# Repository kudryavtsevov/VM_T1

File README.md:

# VM-T1 F1Q — ESP32-C3 Super Mini

Отдельная ветка **`f1q-esp32-c3-super-mini`** для недорогого открытого таймера F1Q.
Исходный проект таймера — **Мстислав**, опубликован с его разрешения под Apache-2.0.
Основная ветка `main` сохраняет исходный проект ESP32-S3; эта ветка использует другую распиновку и логику старта.

## Что подготовлено

- ESP32-C3 Super Mini устанавливается на плату двумя рядами по 8 контактов, шаг 2,54 мм, междурядье 15,24 мм.
- Три сервопривода, отдельный ESC, кнопки ARM/START/OFF/RC DT.
- INA226: ток, напряжение, энергия; BMP280: относительная высота и максимум.
- Экспериментальный лимиттер по энергии и времени с блокировкой повторного запуска.
- Настройка через Wi-Fi. Концевики BACK/FRONT в F1Q не используются.

**Для двигателя около 7 А нужно физически заменить R100 на R010 (0,01 Ом, от 2 Вт).**
Рабочий предел 7,5 А, диапазон АЦП около 8,19 А. Пусковые пики и нагрев требуют стендового измерения.
Режим F1Q по умолчанию выключен. Это прототип, **одобрения EDIC и аппаратных испытаний нет**.

## Документация и плата

- [Размеры, ориентация двух рядов и GPIO C3](docs/C3_GEOMETRY.md).
- [Подключение R010, BMP280 и порядок испытаний](docs/F1Q.md).
- [Готовые модули в России](docs/BUY_RU.md).
- [KiCad, схема, Gerber и монтажный эскиз платы C3](hardware/c3-supermini-v1/README.md).
- [Лицензия и зависимости](LICENSING.md).

Старые PDF и `hardware/carrier-v1` относятся к исходному таймеру/S3 и не являются инструкцией для C3.

## Arduino IDE

Открыть `VM_T1/VM_T1.ino`. Папка и основной файл должны иметь одинаковое имя `VM_T1`.

1. В менеджер плат добавить `https://espressif.github.io/arduino-esp32/package_esp32_index.json`.
2. Установить **esp32 by Espressif Systems 2.0.11**.
3. Библиотеки: **ESP32Servo 1.1.2**, **ArduinoJson 7.4.3**, **Adafruit BMP280 Library 2.6.8**, **Adafruit BusIO 1.17.4**, **Adafruit Unified Sensor 1.1.15**.
4. Плата **ESP32C3 Dev Module**; USB CDC On Boot **Enabled**, Flash Mode **DIO**, Upload Speed **115200**. PSRAM для C3 не требуется.
5. Verify, затем выбрать порт и Upload. При необходимости входа в загрузчик удержать BOOT, нажать и отпустить RESET, затем отпустить BOOT.

```sh
arduino-cli compile --fqbn "esp32:esp32:esp32c3:CDCOnBoot=cdc,FlashMode=dio,UploadSpeed=115200" VM_T1
```

При включении со снятым ARM точка Wi-Fi работает три минуты. Повторно: снять ARM и держать OFF три секунды.
GPIO9/BOOT не занят периферией. Прошивка отклоняет сборку для S3, чтобы не прошить несовместимую распиновку.
Версии Core 3.x этой проверкой не подтверждены.

## Проверки

Arduino CLI 0.35.3: сборка C3 проверена — 806 276 байт Flash, 39 972 байта RAM. Подробности итоговых проверок — в `hardware/c3-supermini-v1/README.md`.
Автономные тесты расчёта энергии находятся в `tests/`. Проверка геометрии, назначения GPIO и совпадения схемы с платой — `tools/verify_c3.py`.
Проверки на компьютере не заменяют калибровку и испытания физического устройства.

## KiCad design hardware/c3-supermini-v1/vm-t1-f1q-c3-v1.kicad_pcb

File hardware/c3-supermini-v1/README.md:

# VM-T1 F1Q: плата для ESP32-C3 Super Mini

Двухслойный прототип **40,64 × 76,2 мм**, FR-4 1,6 мм, медь 35 мкм.
Контроллер устанавливается непосредственно в **два разъёма 1×8**, расстояние между рядами 15,24 мм, шаг 2,54 мм.
Вид сверху: **USB вверх**, 5V в верхнем правом углу, GPIO5 — в верхнем левом.
[Источник геометрии, ориентация и таблица GPIO](../../docs/C3_GEOMETRY.md).

Штриховой контур показывает ориентировочный габарит модуля; точные посадочные размеры задаются центрами отверстий.
USB и положение контура относительно крайних выводов нужно сверить со своей ревизией платы; рисунок разъёма условный.
Между рядами и под центральной областью антенны задана зона без меди. Испытания радиосвязи не выполнены.

## Файлы

- `vm-t1-f1q-c3-v1.kicad_pro`, `.kicad_sch`, `.kicad_pcb` — проект, схема и разведённая плата KiCad 8.
- `VM_T1_C3.pretty`, `VM_T1_C3.kicad_sym`, таблицы библиотек — локальные библиотеки.
- `gerbers/`, `vm-t1-f1q-c3-v1-gerbers.zip` — Gerber и сверловка для пробного изготовления.
- `assembly.svg`, `assembly.png` — монтажный эскиз, построенный из координат платы.
- `drc.json`, `erc.json` — результаты проверок.

## Комплектующие и подключение

| Обозначение | Что установить / подключить |
|---|---|
| U1 | ESP32-C3 Super Mini, два гнезда 1×8, шаг 2,54 мм |
| J1 | INA226: слева направо 3V3, GND, SDA, SCL |
| J2 | BMP280: слева направо 3V3, GND, SDA, SCL |
| J3 / J4 / J5 | Servo S / R / W: GND, +5V, сигнал |
| J6 | ESC: GND и сигнал; средний контакт питания отсутствует |
| J7 / J8 | ARM / START: GND и сигнал |
| J9 / J10 | OFF / RC DT: GND и сигнал |
| J11 | Управляющий вход модуля активной пищалки: GND и сигнал; питание модуля отдельно |
| J12 | BEC: GND и стабилизированные +5V |
| R1 | 47 кОм, выводной, шаг 7,62 мм — подтяжка сигнала ESC к GND |
| R2 / R3 | 4,7 кОм, выводные, шаг 7,62 мм — подтяжки SDA/SCL к 3,3 В |

Если готовые датчики уже имеют подтяжки I²C, учесть их параллельное соединение: R2/R3 можно не устанавливать при наличии достаточных подтяжек на модулях. SDA GPIO2 должна иметь определённый высокий уровень при старте. Ориентир общего сопротивления подтяжек — 2,2–4,7 кОм; проверить фронты и обмен на своей проводке.

Светодиод используется встроенный в Super Mini. GPIO9/BOOT не подключён к периферии; оба отверстия GPIO8/9 присутствуют для штатной установки модуля. Датчики подключаются короткими проводами и закрепляются отдельно: геометрия их модулей не стандартизирована.

**Ток двигателя 7 А не проходит через эту плату.** Силовую цепь аккумулятор → R010 на INA226 → ESC выполнить отдельно подходящими проводами/контактами. 5V получает только выход BEC. Первоначально ограничить суммарный ток 5-вольтовых цепей платы до 1 А и проверить нагрев/просадки; мощные сервоприводы питать отдельной шиной с общей землёй. Нельзя соединять параллельно два выхода BEC или USB и внешнее питание без развязки.

На плате нет стабилизатора и защиты переполюсовки; монтажных отверстий нет. Использовать изолирующее крепление, исключить смещение модулей и контакт нижних выводов с проводкой. Для первого включения применять источник с ограничением тока.

## Проверки, 30 сентября 2026

- KiCad 8.0.2: **ERC 0, DRC 0, неподключённых цепей 0**.
- `tools/verify_c3.py`: проверены оба ряда 1×8, шаг и междурядье; 12 назначений GPIO без повторений; все 51 внешнее соединение схемы совпадают с фактической платой.
- Arduino CLI 0.35.3, Core 2.0.11: **806 276 байт Flash, 39 972 байта RAM**, успешная сборка. Осталось предупреждение Unicode старого генератора разделов Flash.
- Тесты расчёта энергии пройдены. Монтажный эскиз и экспорт платы просмотрены.

Эти проверки не подтверждают работу на оборудовании, тепловой режим, точность лимиттера или соответствие спортивным требованиям. До полётов выполнить [стендовые испытания](../../docs/F1Q.md). Это не одобренный EDIC лимиттер.

## Воспроизведение

Генератор `tools/generate_c3_carrier.py` запускается Python из KiCad 8. После генерации выполнить ERC/DRC, экспортировать netlist в формате `kicadxml`, затем запустить `tools/verify_c3.py <netlist.xml>` тем же Python. После изменений платы заново экспортировать Gerber и сверловку. Дорожки сигналов 0,3 мм, питания 0,8 мм, минимальный зазор 0,2 мм, сверловка выводов 1,0 мм, переходных отверстий 0,3 мм.

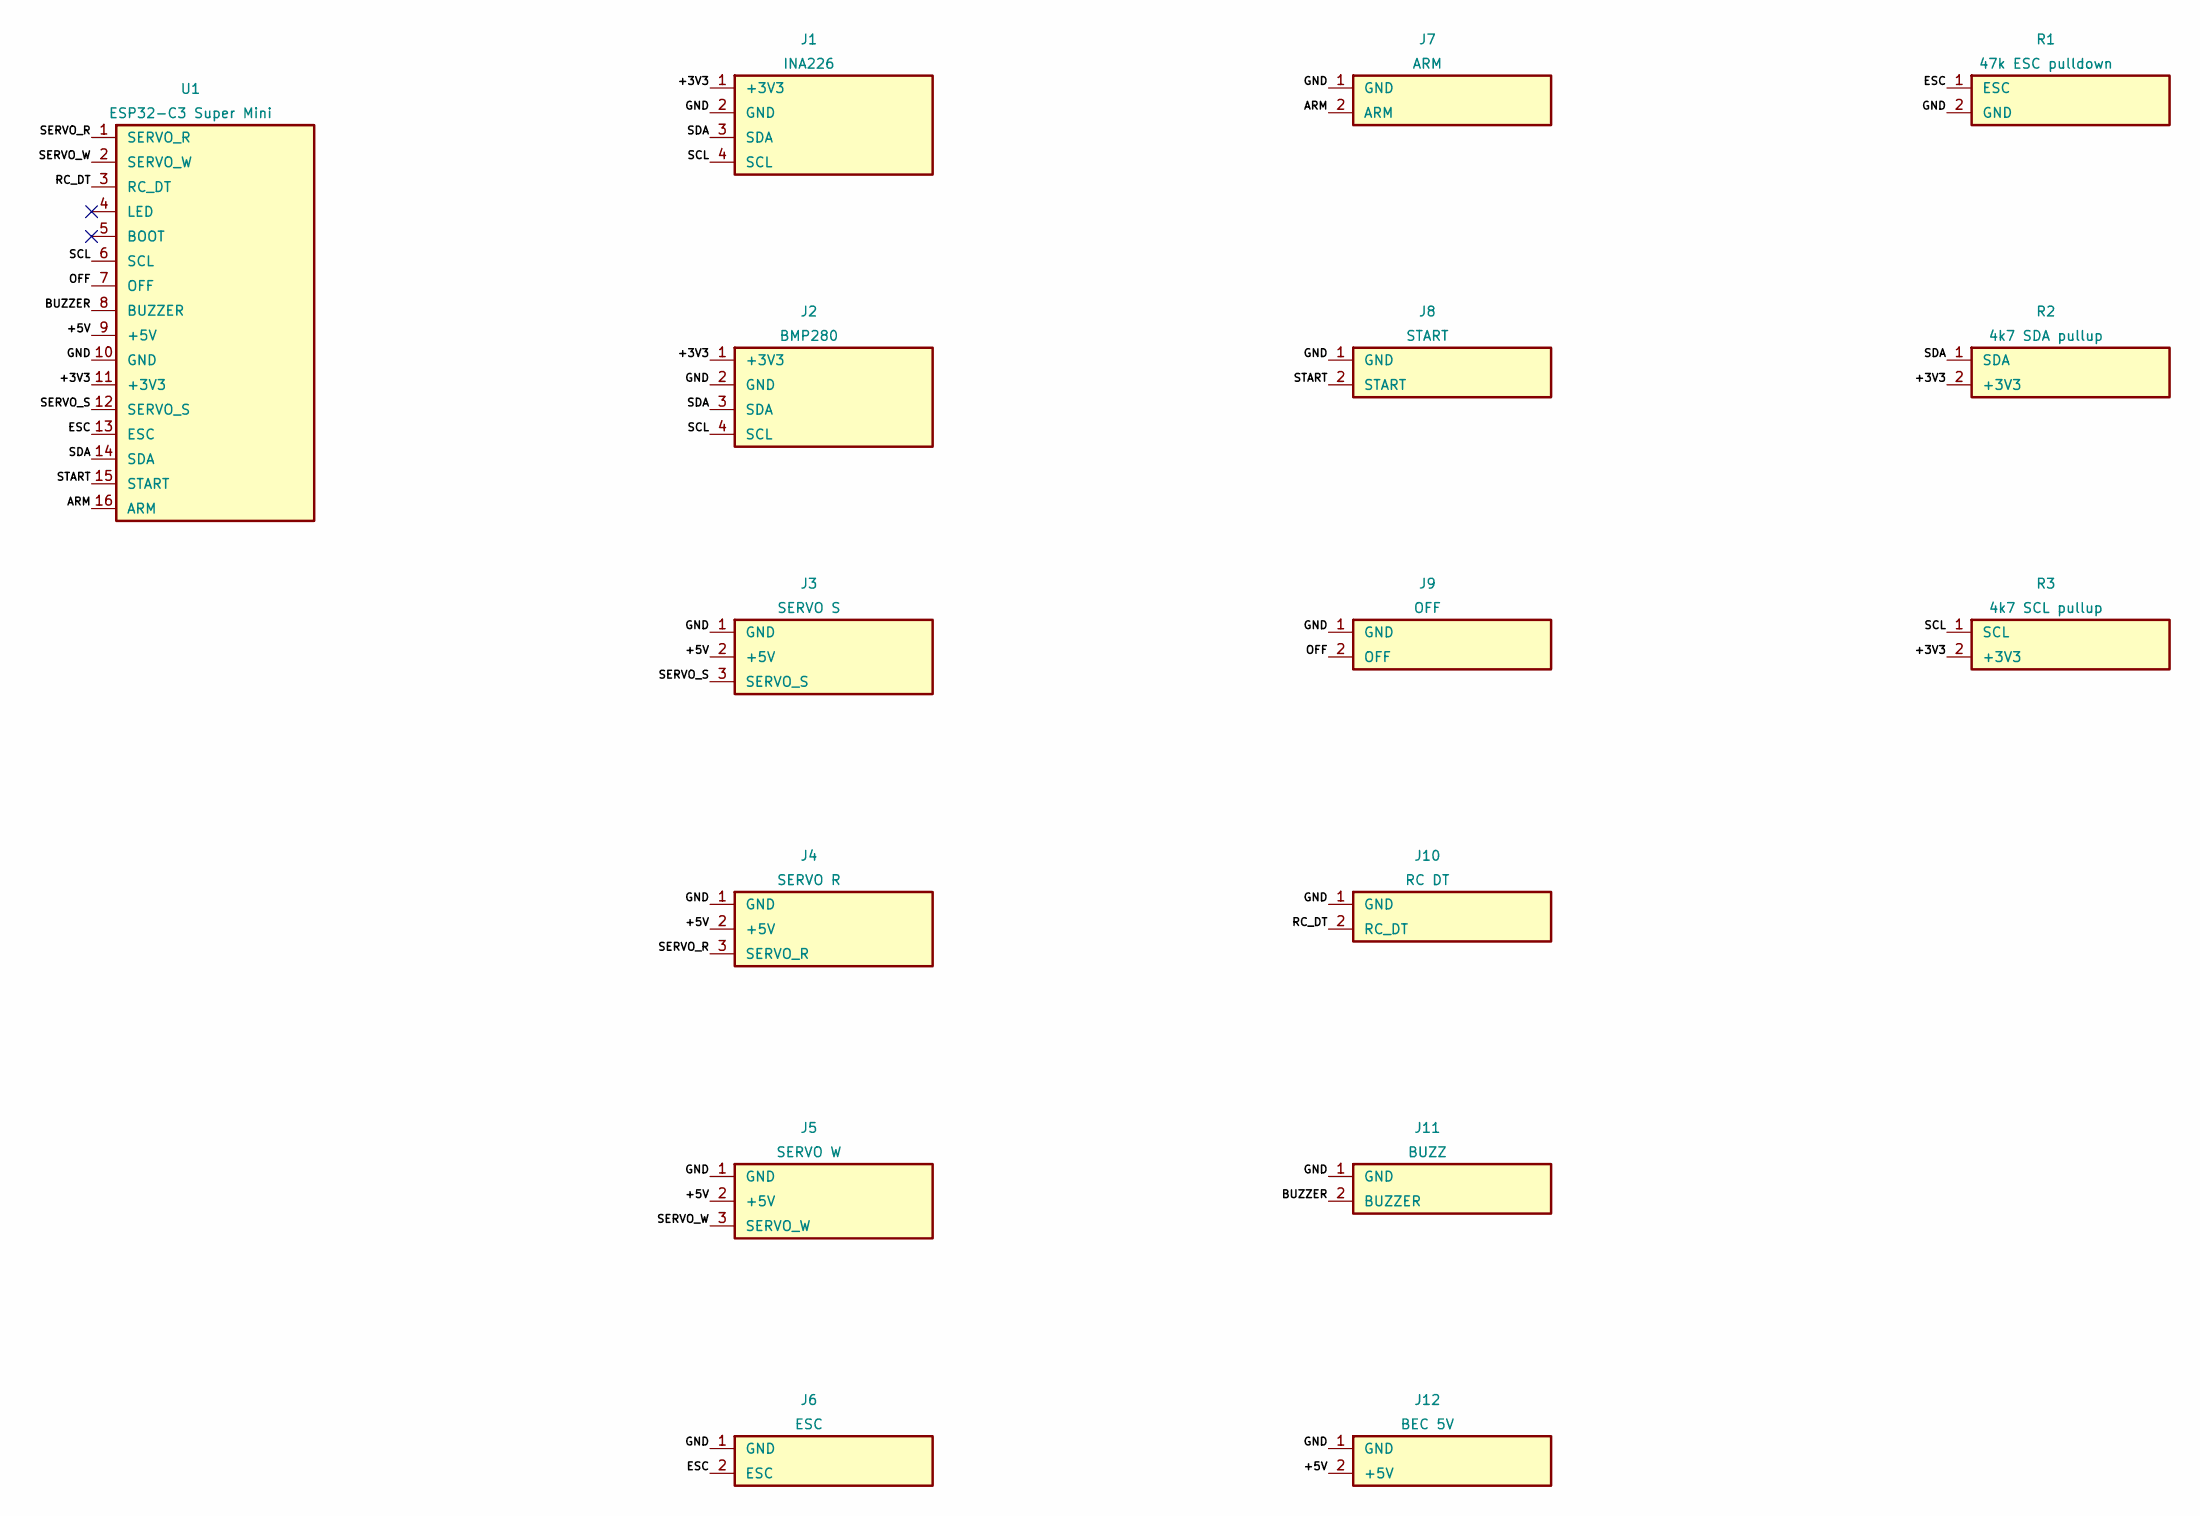
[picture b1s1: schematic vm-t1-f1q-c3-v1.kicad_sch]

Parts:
J1: INA226; J1
J2: BMP280; J2
J3: SERVO S; J3
J4: SERVO R; J4
J5: SERVO W; J5
J6: ESC; J6
J7: ARM; J7
J8: START; J8
J9: OFF; J9
J10: RC DT; J10
J11: BUZZ; J11
J12: BEC 5V; J12
R1: 47k ESC pulldown; R1
R2: 4k7 SDA pullup; R2
R3: 4k7 SCL pullup; R3
U1: ESP32-C3 Super Mini; U1

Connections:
+3V3: J1.1 (+3V3), J2.1 (+3V3), R2.2 (+3V3), R3.2 (+3V3), U1.11 (+3V3)
+5V: J3.2 (+5V), J4.2 (+5V), J5.2 (+5V), J12.2 (+5V), U1.9 (+5V)
ARM: J7.2 (ARM), U1.16 (ARM)
BOOT: U1.5 (BOOT)
BUZZER: J11.2 (BUZZER), U1.8 (BUZZER)
ESC: J6.2 (ESC), R1.1 (ESC), U1.13 (ESC)
GND: J1.2 (GND), J2.2 (GND), J3.1 (GND), J4.1 (GND), J5.1 (GND), J6.1 (GND), J7.1 (GND), J8.1 (GND), J9.1 (GND), J10.1 (GND), J11.1 (GND), J12.1 (GND), R1.2 (GND), U1.10 (GND)
LED: U1.4 (LED)
OFF: J9.2 (OFF), U1.7 (OFF)
RC_DT: J10.2 (RC_DT), U1.3 (RC_DT)
SCL: J1.4 (SCL), J2.4 (SCL), R3.1 (SCL), U1.6 (SCL)
SDA: J1.3 (SDA), J2.3 (SDA), R2.1 (SDA), U1.14 (SDA)
SERVO_R: J4.3 (SERVO_R), U1.1 (SERVO_R)
SERVO_S: J3.3 (SERVO_S), U1.12 (SERVO_S)
SERVO_W: J5.3 (SERVO_W), U1.2 (SERVO_W)
START: J8.2 (START), U1.15 (START)

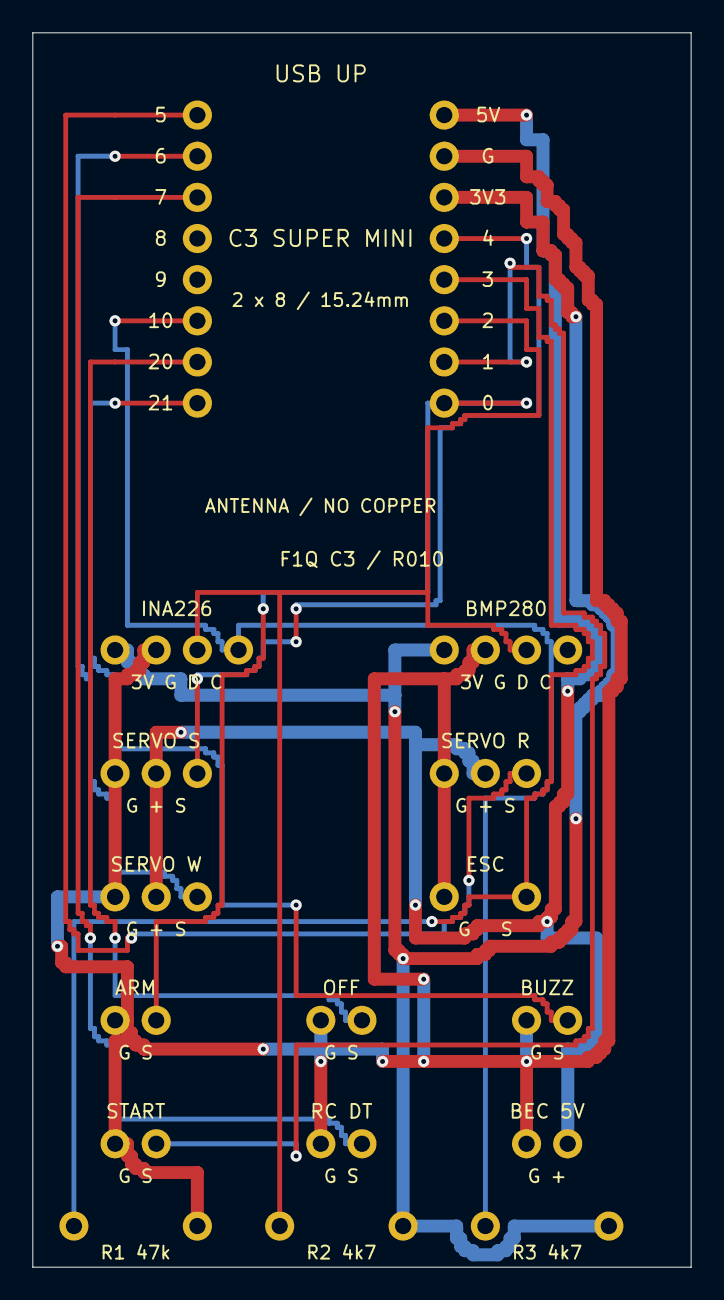
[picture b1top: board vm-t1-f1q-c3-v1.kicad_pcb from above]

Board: 2 copper layers, 40.6 x 76.2 mm, 16 parts (0 on the bottom side), 14 nets.

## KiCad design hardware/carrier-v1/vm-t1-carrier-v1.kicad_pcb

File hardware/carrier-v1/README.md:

> Архивный прототип для ESP32-S3 с проводами. Для текущей ветки C3 используйте [c3-supermini-v1](../c3-supermini-v1/README.md).

# VM-T1: выводная плата-переходник v1

Инженерный прототип 30 × 100 мм, 2 слоя, FR-4 1,6 мм, медь 35 мкм. Датчики и ESP подключаются короткими проводами и крепятся отдельно. Это универсальная распайка, а не посадочные места конкретных модулей: покупать одинаковый вариант Arduino-модуля не требуется. Для установки непосредственно на плату нужны точные размеры ваших модулей.

- `vm-t1-carrier-v1.kicad_pro` — открыть в KiCad 8.
- `vm-t1-carrier-v1.kicad_sch` / `.kicad_pcb` — схема и разведённая плата.
- `VM_T1.pretty`, `VM_T1.kicad_sym` и таблицы библиотек — локальные библиотеки.
- `gerbers/` и `vm-t1-carrier-v1-gerbers.zip` — Gerber и сверловка прототипа.
- `assembly.svg` / `assembly.png` — монтажный эскиз сверху; координаты взяты из генератора платы.
- `drc.json`, `erc.json` — проверки KiCad, ноль нарушений; это не подтверждение работы устройства на стенде.

## Сборка

Слева J1 — отдельные провода к ESP (не стандартная гребёнка ESP32). Справа — провода к периферии. Для серво порядок слева направо GND / +5V / сигнал. Для кнопок — GND / сигнал. INA226 J19 и BMP280 J20: сверху вниз 3V3, GND, SDA, SCL, шаг 2,54 мм. Не переносить этот порядок без проверки на разъём самого модуля.

R1 — выводной резистор 47 кОм, шаг 7,62 мм; он подтягивает ESC к GND при старте процессора. Светодиод подключать через внешний 1 кОм; пищалку — через готовый драйвер. На плате нет стабилизатора, защиты переполюсовки и собственных подтяжек I²C: проверить наличие 3,3-вольтовых подтяжек на модулях.

Питание — стабилизированные 5 В от BEC. Для первого прототипа ограничить суммарную нагрузку шины BEC на плате до 1 А, проверить нагрев и просадки при работе серво. Более мощные сервоприводы питать отдельной проводной шиной с общей землёй. Силовую цепь аккумулятор → R010 → ESC прокладывать **вне этой платы**. На неё нельзя заводить ток двигателя 7 А или напряжение аккумулятора на шину 5 В.

Плату закреплять изолирующим креплением: монтажных отверстий нет. Оставить свободное пространство у антенны ESP и доступ воздуха к BMP280; исключить обдув винтом и свет на кристалл датчика. После изготовления проверить прозвонкой, затем запитать от источника с ограничением тока.

## Проверки и воспроизведение

Генератор: `tools/generate_carrier.py`, запуск Python из KiCad 8 с модулем pcbnew. После изменений повторить DRC/ERC, экспорт Gerber и сверловки. Текущая схема содержит разъёмы внешних модулей, а не их внутренние схемы. Проверены 59 соответствий контакт–цепь экспортированной схемы и платы. Зазор ≥0,2 мм, дорожки ≥0,3 мм, сверловка контактных площадок 0,9 мм; переходные отверстия 0,3 мм. DRC не проверяет силовую пригодность готового INA226-модуля.

Производственные файлы подготовлены для пробного экземпляра. Размеры модулей, пусковой ток, нагрев шунта и контактов ещё не подтверждены на вашем оборудовании. См. [подключение и испытания](../../docs/F1Q.md).

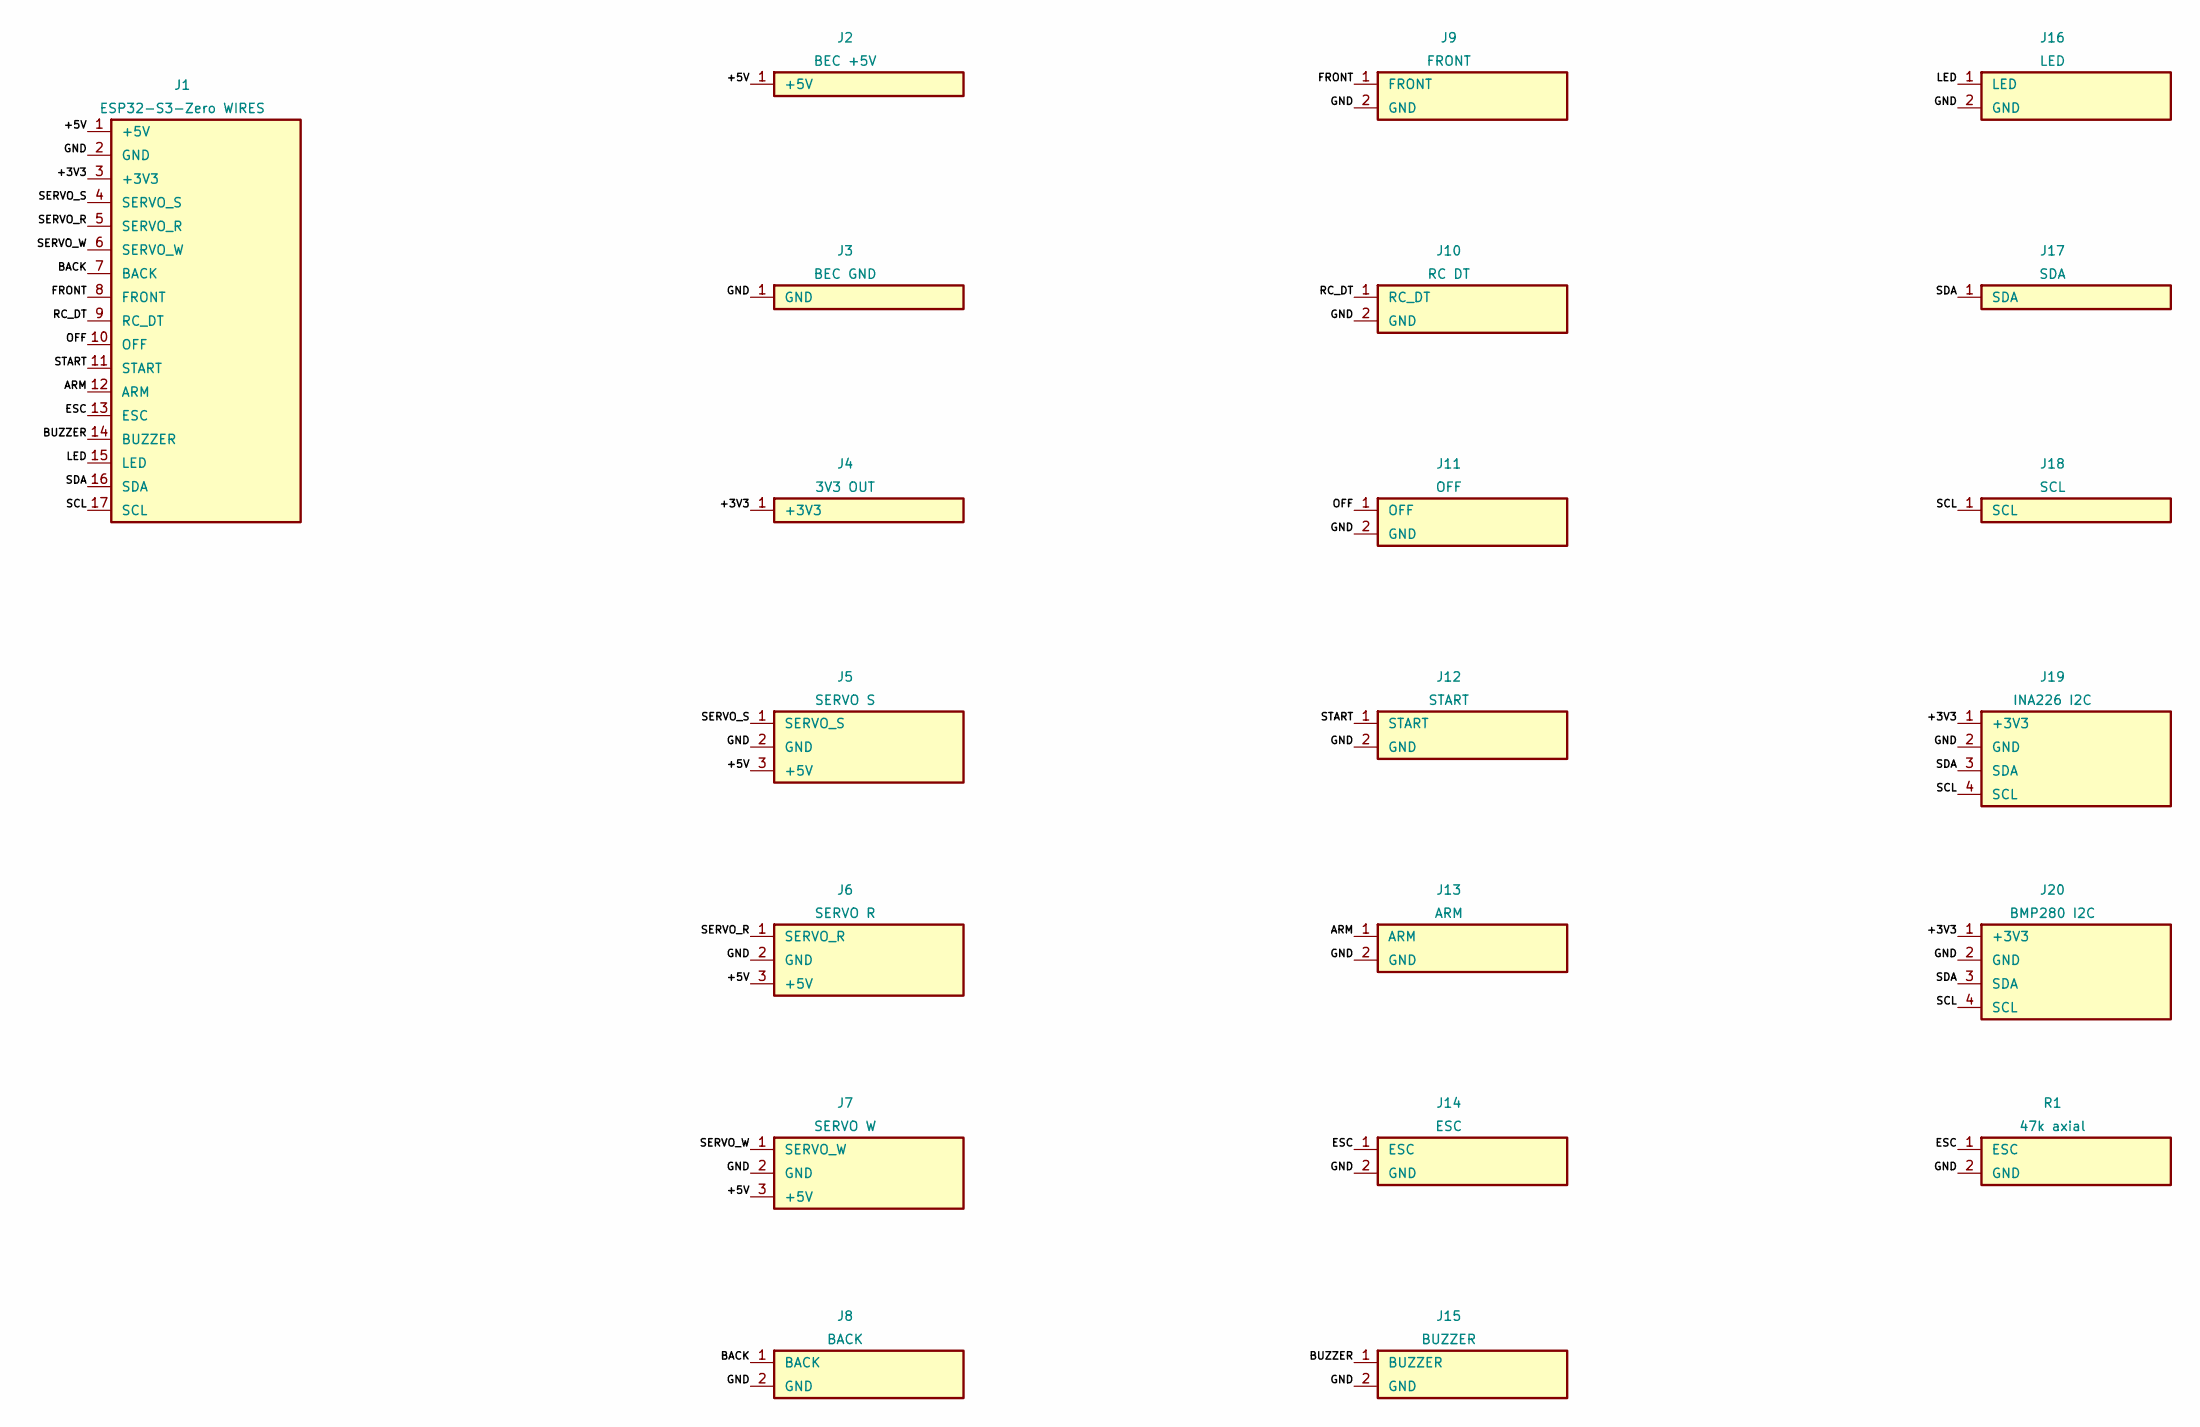
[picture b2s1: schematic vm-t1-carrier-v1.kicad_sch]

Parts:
J1: ESP32-S3-Zero WIRES; J1
J2: BEC +5V; J2
J3: BEC GND; J3
J4: 3V3 OUT; J4
J5: SERVO S; J5
J6: SERVO R; J6
J7: SERVO W; J7
J8: BACK; J8
J9: FRONT; J9
J10: RC DT; J10
J11: OFF; J11
J12: START; J12
J13: ARM; J13
J14: ESC; J14
J15: BUZZER; J15
J16: LED; J16
J17: SDA; J17
J18: SCL; J18
J19: INA226 I2C; J19
J20: BMP280 I2C; J20
R1: 47k axial; R1

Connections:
+3V3: J1.3 (+3V3), J4.1, J19.1 (+3V3), J20.1 (+3V3)
+5V: J1.1 (+5V), J2.1, J5.3 (+5V), J6.3 (+5V), J7.3 (+5V)
ARM: J1.12 (ARM), J13.1 (ARM)
BACK: J1.7 (BACK), J8.1 (BACK)
BUZZER: J1.14 (BUZZER), J15.1 (BUZZER)
ESC: J1.13 (ESC), J14.1 (ESC), R1.1 (ESC)
FRONT: J1.8 (FRONT), J9.1 (FRONT)
GND: J1.2 (GND), J3.1, J5.2 (GND), J6.2 (GND), J7.2 (GND), J8.2 (GND), J9.2 (GND), J10.2 (GND), J11.2 (GND), J12.2 (GND), J13.2 (GND), J14.2 (GND), J15.2 (GND), J16.2 (GND), J19.2 (GND), J20.2 (GND), R1.2 (GND)
LED: J1.15 (LED), J16.1 (LED)
OFF: J1.10 (OFF), J11.1 (OFF)
RC_DT: J1.9 (RC_DT), J10.1 (RC_DT)
SCL: J1.17 (SCL), J18.1, J19.4 (SCL), J20.4 (SCL)
SDA: J1.16 (SDA), J17.1, J19.3 (SDA), J20.3 (SDA)
SERVO_R: J1.5 (SERVO_R), J6.1 (SERVO_R)
SERVO_S: J1.4 (SERVO_S), J5.1 (SERVO_S)
SERVO_W: J1.6 (SERVO_W), J7.1 (SERVO_W)
START: J1.11 (START), J12.1 (START)

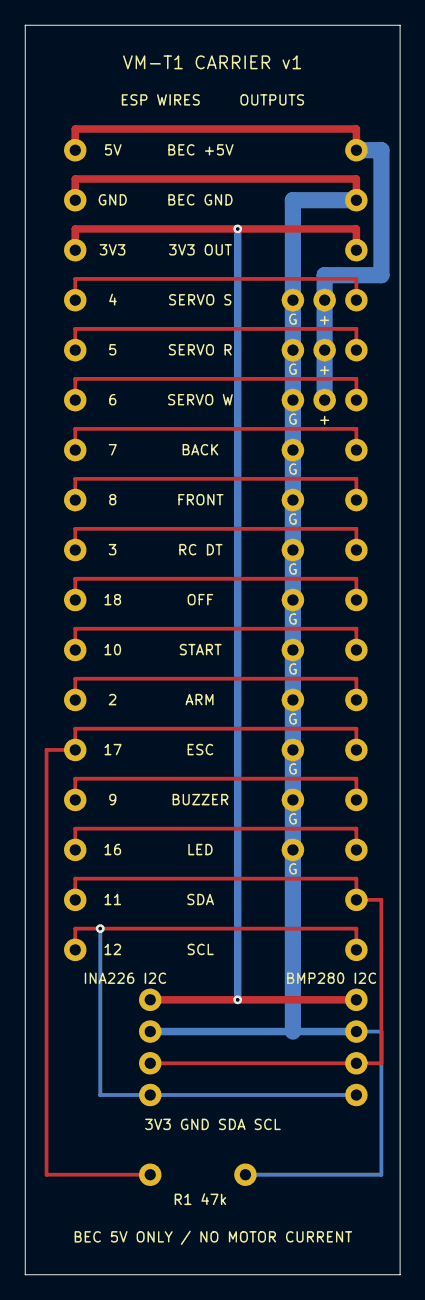
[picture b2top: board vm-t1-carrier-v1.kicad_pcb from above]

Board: 2 copper layers, 30.0 x 100.0 mm, 21 parts (0 on the bottom side), 17 nets.

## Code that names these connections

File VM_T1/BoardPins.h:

// SPDX-License-Identifier: Apache-2.0
#pragma once
#if !defined(CONFIG_IDF_TARGET_ESP32C3)
#error "This F1Q branch requires ESP32C3 Dev Module, not ESP32-S3."
#endif
constexpr int PIN_SERVO_S=4, PIN_SERVO_R=5, PIN_SERVO_W=6;
constexpr int PIN_ESC=3, PIN_ARM=0, PIN_START=1;
constexpr int PIN_RC_DT=7, PIN_OFF_BUTTON=20, PIN_BUZZER=21;
constexpr int PIN_LED=8, PIN_SDA=2, PIN_SCL=10;
// GPIO8 onboard blue LED is active LOW. GPIO9/BOOT stays unused.
inline void statusLed(bool on) { digitalWrite(PIN_LED,on ? LOW : HIGH); }
